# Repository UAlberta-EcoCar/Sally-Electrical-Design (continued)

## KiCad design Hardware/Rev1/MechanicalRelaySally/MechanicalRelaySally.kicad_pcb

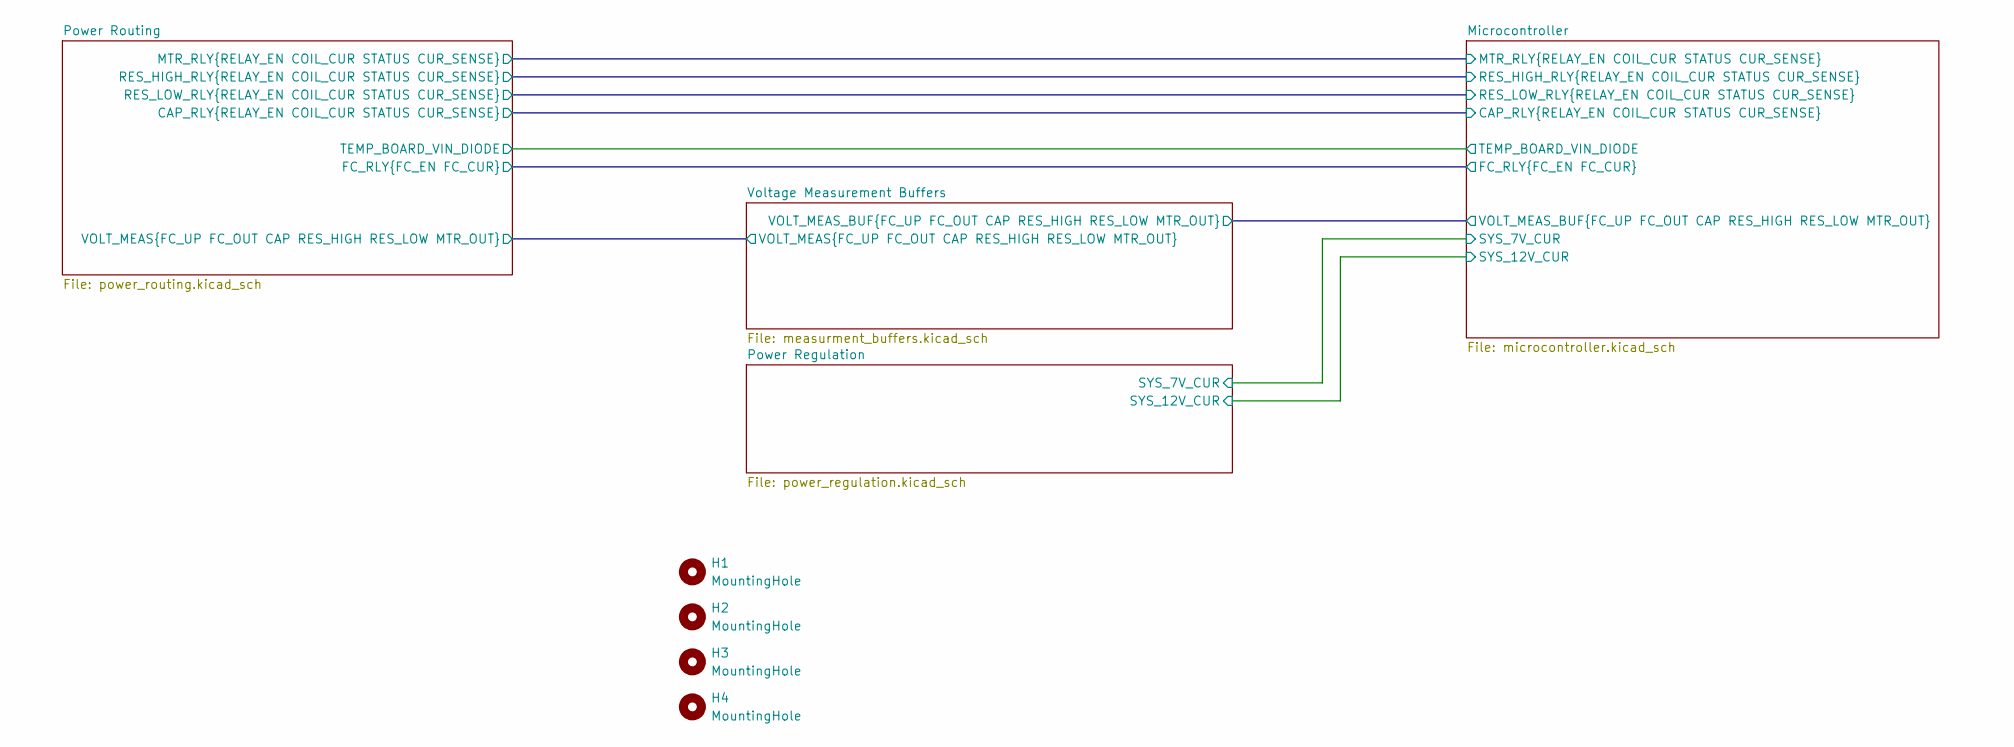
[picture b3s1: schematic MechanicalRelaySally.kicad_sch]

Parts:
H1, H2, H3, H4: MountingHole; MountingHole_3mm_Pad_Via

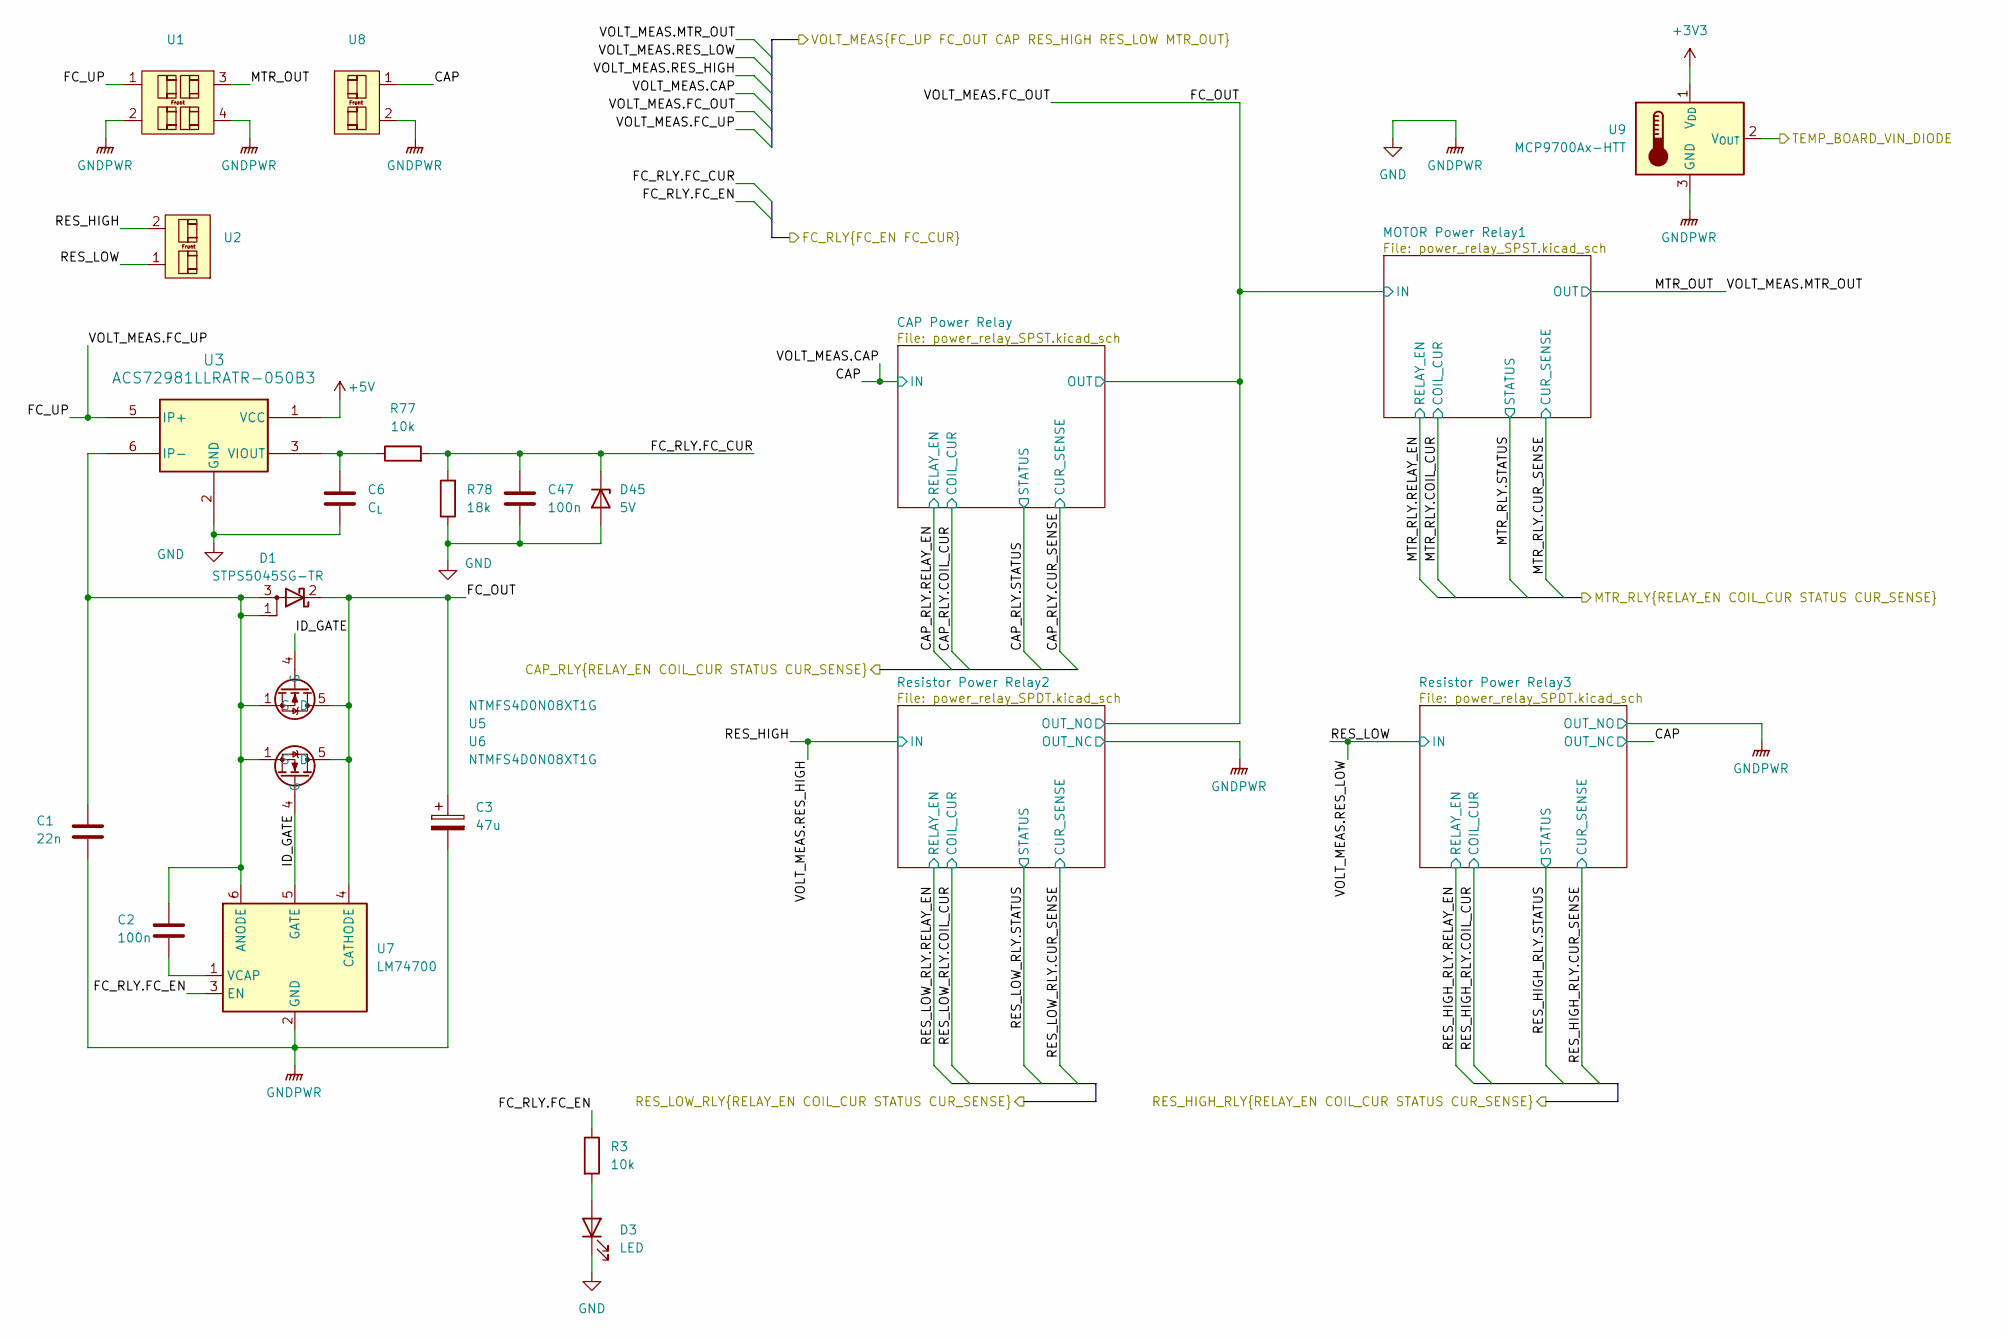
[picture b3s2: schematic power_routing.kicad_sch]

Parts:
C1: 22n; C_1210_3225Metric
C2: 100n; C_0603_1608Metric
C3: 47u; CP_Elec_6.3x7.7
C6: C_{L}; C_0402_1005Metric
C47: 100n; C_0402_1005Metric
D1: STPS5045SG-TR; TO-263-2; Part# 497-13279-1-ND
D3: LED; LED_0603_1608Metric
D45: 5V; D_SOD-323F
R3, R77: 10k; R_0603_1608Metric
R78: 18k; R_0603_1608Metric
U1: PowerPole15-45BoardEdge2x2
U2, U8: PowerPole15-45BoardEdge2x1
U3: ACS72981LLRATR-050B3; XDCR_ACS72981LLRATR-100B5
U5, U6: NTMFS4D0N08XT1G; PowerMosDFNHybrid
U7: LM74700; SOT-23-6
U9: MCP9700Ax-HTT; SOT-23

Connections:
+3V3: U9.1 (V_{DD}); also elsewhere on the board
+5V: U3.1 (VCC); also elsewhere on the board
/Microcontroller/FC_RLY.FC_CUR: C47.1, D45.1 (K), R77.2, R78.2; also elsewhere on the board
/Microcontroller/FC_RLY.FC_EN: R3.1, U7.3 (EN); also elsewhere on the board
/Microcontroller/TEMP_BOARD_VIN_DIODE: U9.2 (V_{OUT}); also elsewhere on the board
/Power Routing/ID_GATE: U5.4 (G), U6.4 (G), U7.5 (GATE)
/Power Routing/VOLT_MEAS.CAP: U8.1; also elsewhere on the board
/Power Routing/VOLT_MEAS.FC_OUT: C3.1, D1.2 (K), U5.5 (D), U6.5 (D), U7.4 (CATHODE); also elsewhere on the board
/Power Routing/VOLT_MEAS.FC_UP: U1.1, U3.5 (IP+); also elsewhere on the board
/Power Routing/VOLT_MEAS.MTR_OUT: U1.3; also elsewhere on the board
/Power Routing/VOLT_MEAS.RES_HIGH: U2.2; also elsewhere on the board
/Power Routing/VOLT_MEAS.RES_LOW: U2.1; also elsewhere on the board
GND: C1.2, C3.2, C6.2, C47.2, D3.1 (K), D45.2 (A), R78.1, U1.2, U1.4, U3.2 (GND), U3.4 (NC), U7.2 (GND), U8.2, U9.3 (GND); also elsewhere on the board
unnamed: D3.2 (A), R3.2
unnamed: C1.1, C2.1, D1.1 (A), D1.3 (A), U3.6 (IP-), U5.1 (S), U5.2 (S), U5.3 (S), U6.1 (S), U6.2 (S), U6.3 (S), U7.6 (ANODE)
unnamed: C6.1, R77.1, U3.3 (VIOUT)
unnamed: C2.2, U7.1 (VCAP)

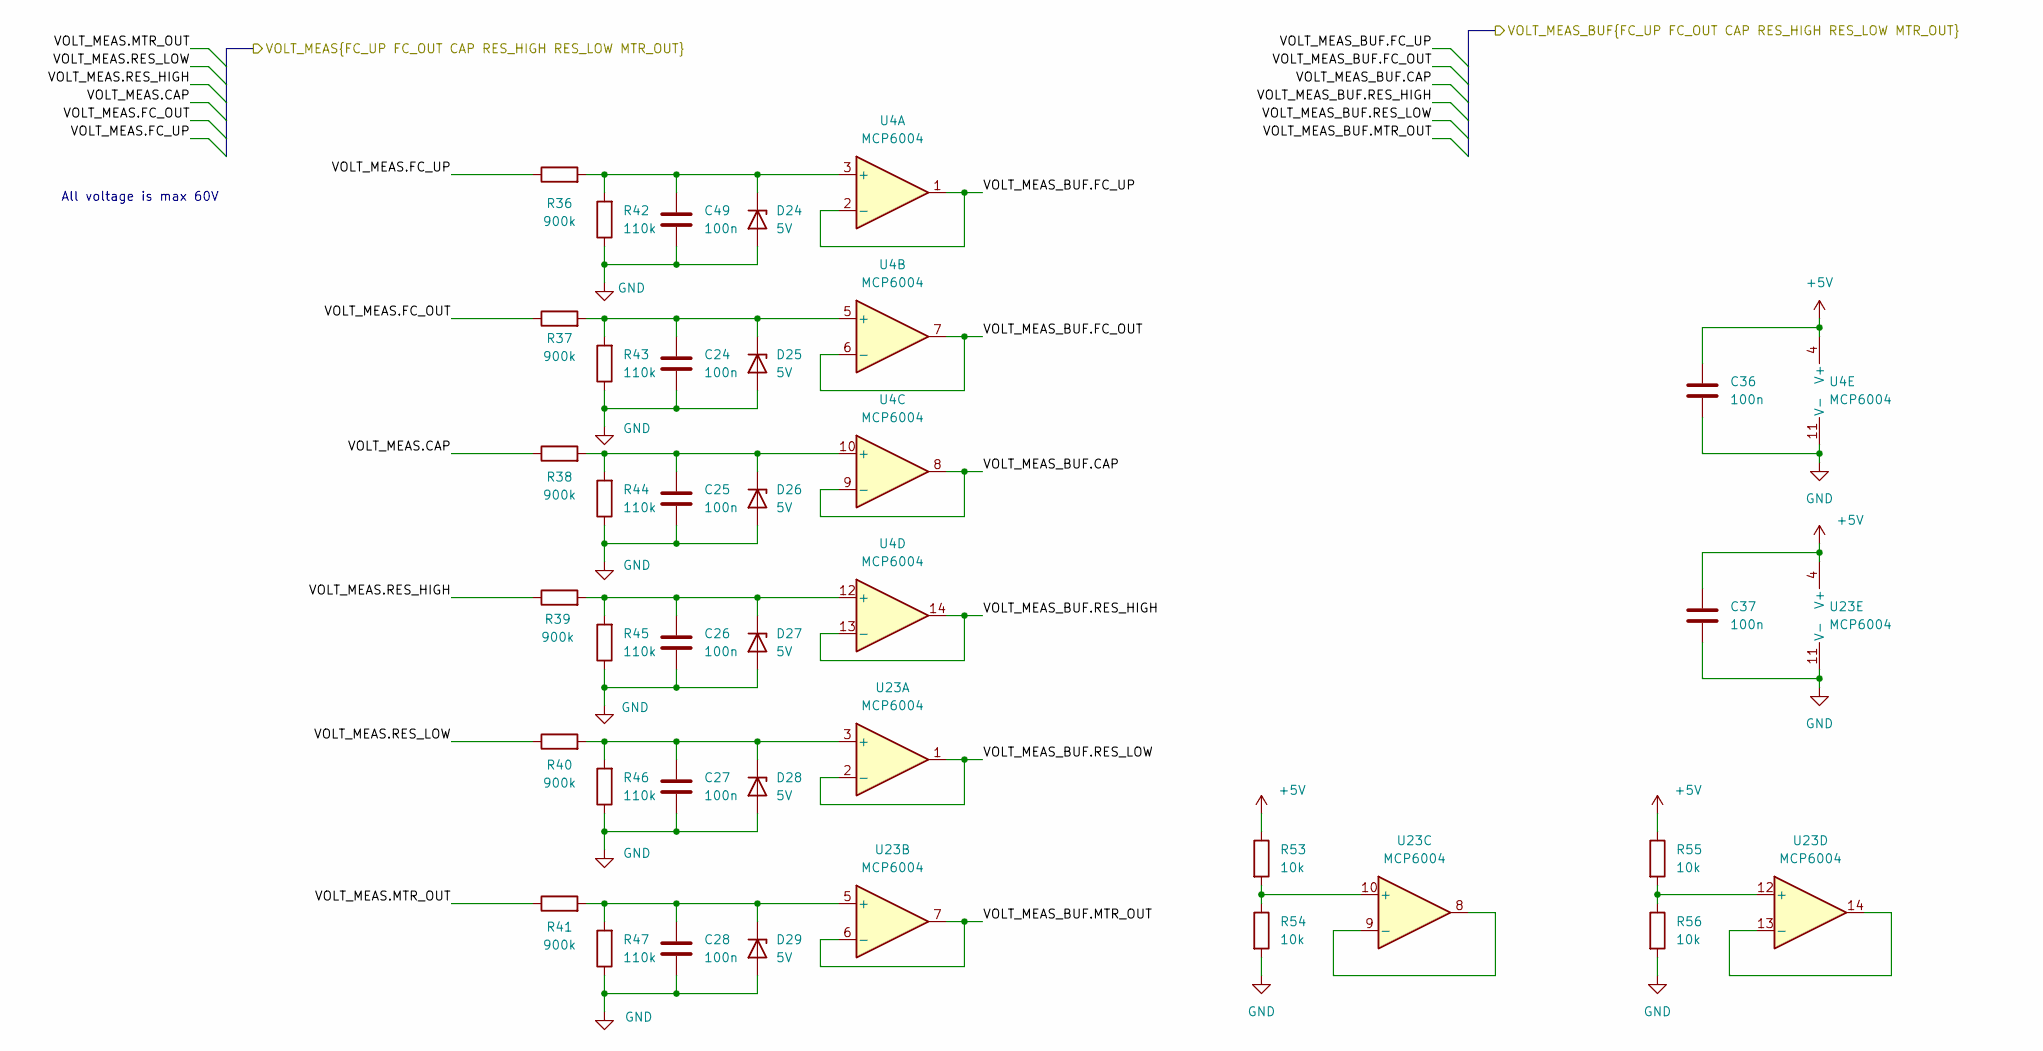
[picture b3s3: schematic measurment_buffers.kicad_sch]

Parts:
C24, C25, C26, C27, C28, C36, C37, C49: 100n; C_0402_1005Metric
D24, D25, D26, D27, D28, D29: 5V; D_SOD-323F
R36, R37, R38, R39, R40, R41: 900k; R_0603_1608Metric
R42, R43, R44, R45, R46, R47: 110k; R_0603_1608Metric
R53, R54, R55, R56: 10k; R_0603_1608Metric
U4, U23: MCP6004; TSSOP-14_4.4x5mm_P0.65mm

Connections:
+5V: C36.1, C37.1, R53.1, R55.1, U4.4 (V+), U23.4 (V+); also elsewhere on the board
/Microcontroller/VOLT_MEAS_BUF.CAP: U4.8, U4.9 (-); also elsewhere on the board
/Microcontroller/VOLT_MEAS_BUF.FC_OUT: U4.6 (-), U4.7; also elsewhere on the board
/Microcontroller/VOLT_MEAS_BUF.FC_UP: U4.1, U4.2 (-); also elsewhere on the board
/Microcontroller/VOLT_MEAS_BUF.MTR_OUT: U23.6 (-), U23.7; also elsewhere on the board
/Microcontroller/VOLT_MEAS_BUF.RES_HIGH: U4.13 (-), U4.14; also elsewhere on the board
/Microcontroller/VOLT_MEAS_BUF.RES_LOW: U23.1, U23.2 (-); also elsewhere on the board
/Power Routing/VOLT_MEAS.CAP: R38.1; also elsewhere on the board
/Power Routing/VOLT_MEAS.FC_OUT: R37.1; also elsewhere on the board
/Power Routing/VOLT_MEAS.FC_UP: R36.1; also elsewhere on the board
/Power Routing/VOLT_MEAS.MTR_OUT: R41.1; also elsewhere on the board
/Power Routing/VOLT_MEAS.RES_HIGH: R39.1; also elsewhere on the board
/Power Routing/VOLT_MEAS.RES_LOW: R40.1; also elsewhere on the board
GND: C24.2, C25.2, C26.2, C27.2, C28.2, C36.2, C37.2, C49.2, D24.2 (A), D25.2 (A), D26.2 (A), D27.2 (A), D28.2 (A), D29.2 (A), R42.1, R43.1, R44.1, R45.1, R46.1, R47.1, R54.2, R56.2, U4.11 (V-), U23.11 (V-); also elsewhere on the board
unnamed: C49.1, D24.1 (K), R36.2, R42.2, U4.3 (+)
unnamed: C24.1, D25.1 (K), R37.2, R43.2, U4.5 (+)
unnamed: C25.1, D26.1 (K), R38.2, R44.2, U4.10 (+)
unnamed: C26.1, D27.1 (K), R39.2, R45.2, U4.12 (+)
unnamed: C27.1, D28.1 (K), R40.2, R46.2, U23.3 (+)
unnamed: C28.1, D29.1 (K), R41.2, R47.2, U23.5 (+)
unnamed: R53.2, R54.1, U23.10 (+)
unnamed: U23.8, U23.9 (-)
unnamed: R55.2, R56.1, U23.12 (+)
unnamed: U23.13 (-), U23.14

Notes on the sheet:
All voltage is max 60V

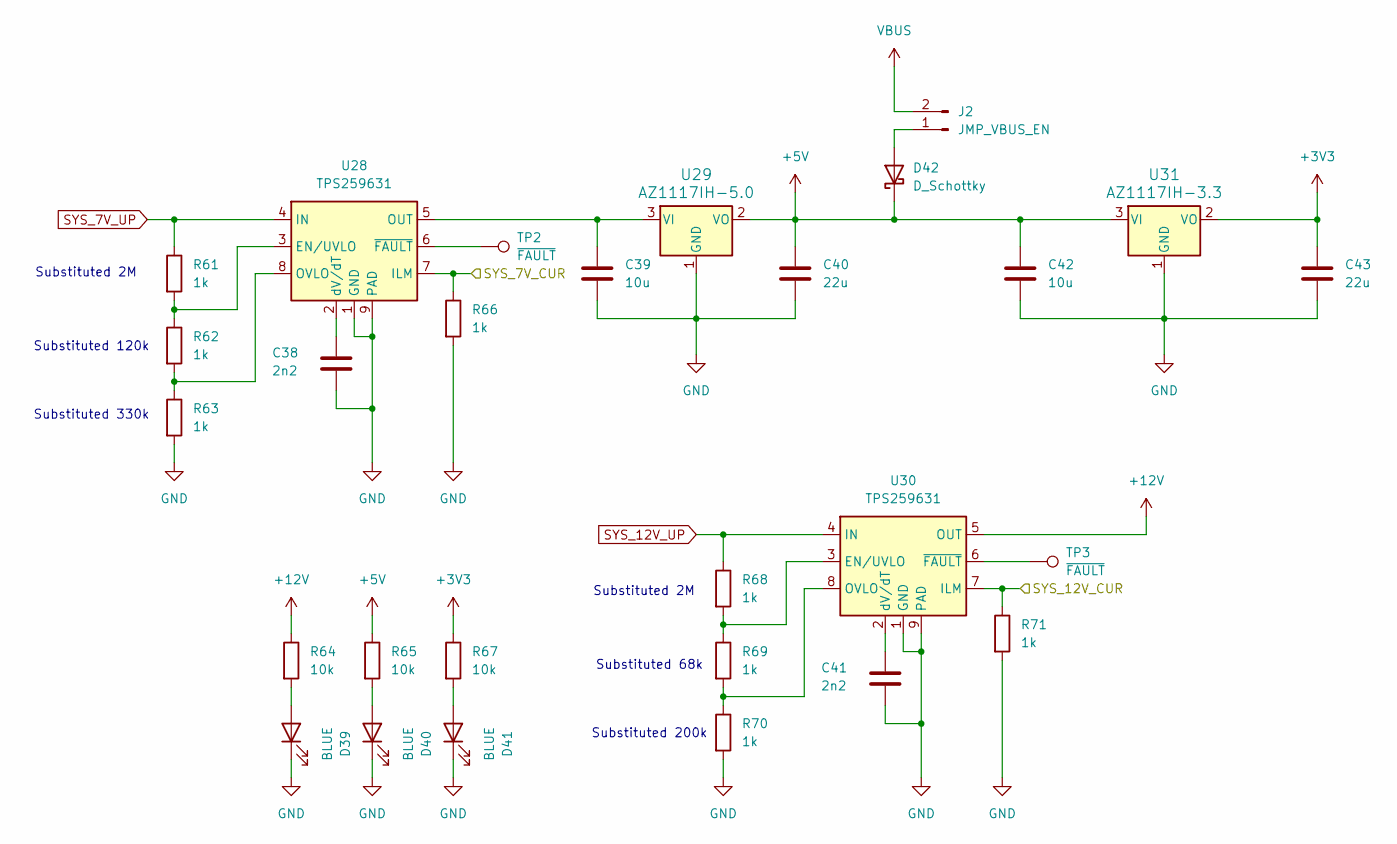
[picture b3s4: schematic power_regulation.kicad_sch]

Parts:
C38, C41: 2n2; C_0402_1005Metric
C39: 10u; C_0603_1608Metric
C40: 22u; C_0603_1608Metric
C42: 10u; C_0805_2012Metric
C43: 22u; C_0805_2012Metric
D39, D40, D41: BLUE; LED_0603_1608Metric
D42: D_Schottky; D_SOD-123
J2: JMP_VBUS_EN; PinHeader_1x02_P2.54mm_Horizontal
R61, R62, R63, R66, R68, R69, R70, R71: 1k; R_0603_1608Metric
R64, R65, R67: 10k; R_0603_1608Metric
TP2, TP3: ~{FAULT}; TestPoint_Pad_1.0x1.0mm
U28, U30: TPS259631; SOIC-8-1EP_3.9x4.9mm_P1.27mm_EP2.29x3mm
U29: AZ1117IH-5.0; SOT-223-3_TabPin2
U31: AZ1117IH-3.3; SOT-223-3_TabPin2

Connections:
+3V3: C43.1, R67.1, U31.2 (VO); also elsewhere on the board
+5V: C40.1, C42.1, D42.1 (K), R65.1, U29.2 (VO), U31.3 (VI); also elsewhere on the board
+12V: R64.1, U30.5 (OUT); also elsewhere on the board
/Microcontroller/SYS_7V_CUR: R66.1, U28.7 (ILM); also elsewhere on the board
/Microcontroller/SYS_12V_CUR: R71.1, U30.7 (ILM); also elsewhere on the board
GND: C38.2, C39.2, C40.2, C41.2, C42.2, C43.2, D39.1 (K), D40.1 (K), D41.1 (K), R63.2, R66.2, R70.2, R71.2, U28.1 (GND), U28.9 (PAD), U29.1 (GND), U30.1 (GND), U30.9 (PAD), U31.1 (GND); also elsewhere on the board
unnamed: D39.2 (A), R64.2
unnamed: D40.2 (A), R65.2
unnamed: D41.2 (A), R67.2
unnamed: D42.2 (A), J2.1
unnamed: R61.2, R62.1, U28.3 (EN/UVLO)
unnamed: C39.1, U28.5 (OUT), U29.3 (VI)
unnamed: R62.2, R63.1, U28.8 (OVLO)
unnamed: C38.1, U28.2 (dV/dT)
unnamed: TP2.1, U28.6 (~FAULT)
unnamed: R68.2, R69.1, U30.3 (EN/UVLO)
unnamed: R69.2, R70.1, U30.8 (OVLO)
unnamed: C41.1, U30.2 (dV/dT)
unnamed: TP3.1, U30.6 (~FAULT)
SYS_7V_UP: R61.1, U28.4 (IN); also elsewhere on the board
SYS_12V_UP: R68.1, U30.4 (IN); also elsewhere on the board
VBUS: J2.2; also elsewhere on the board

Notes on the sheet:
Substituted 200k
Substituted 2M
Substituted 330k
Substituted 68k
Substituted 120k

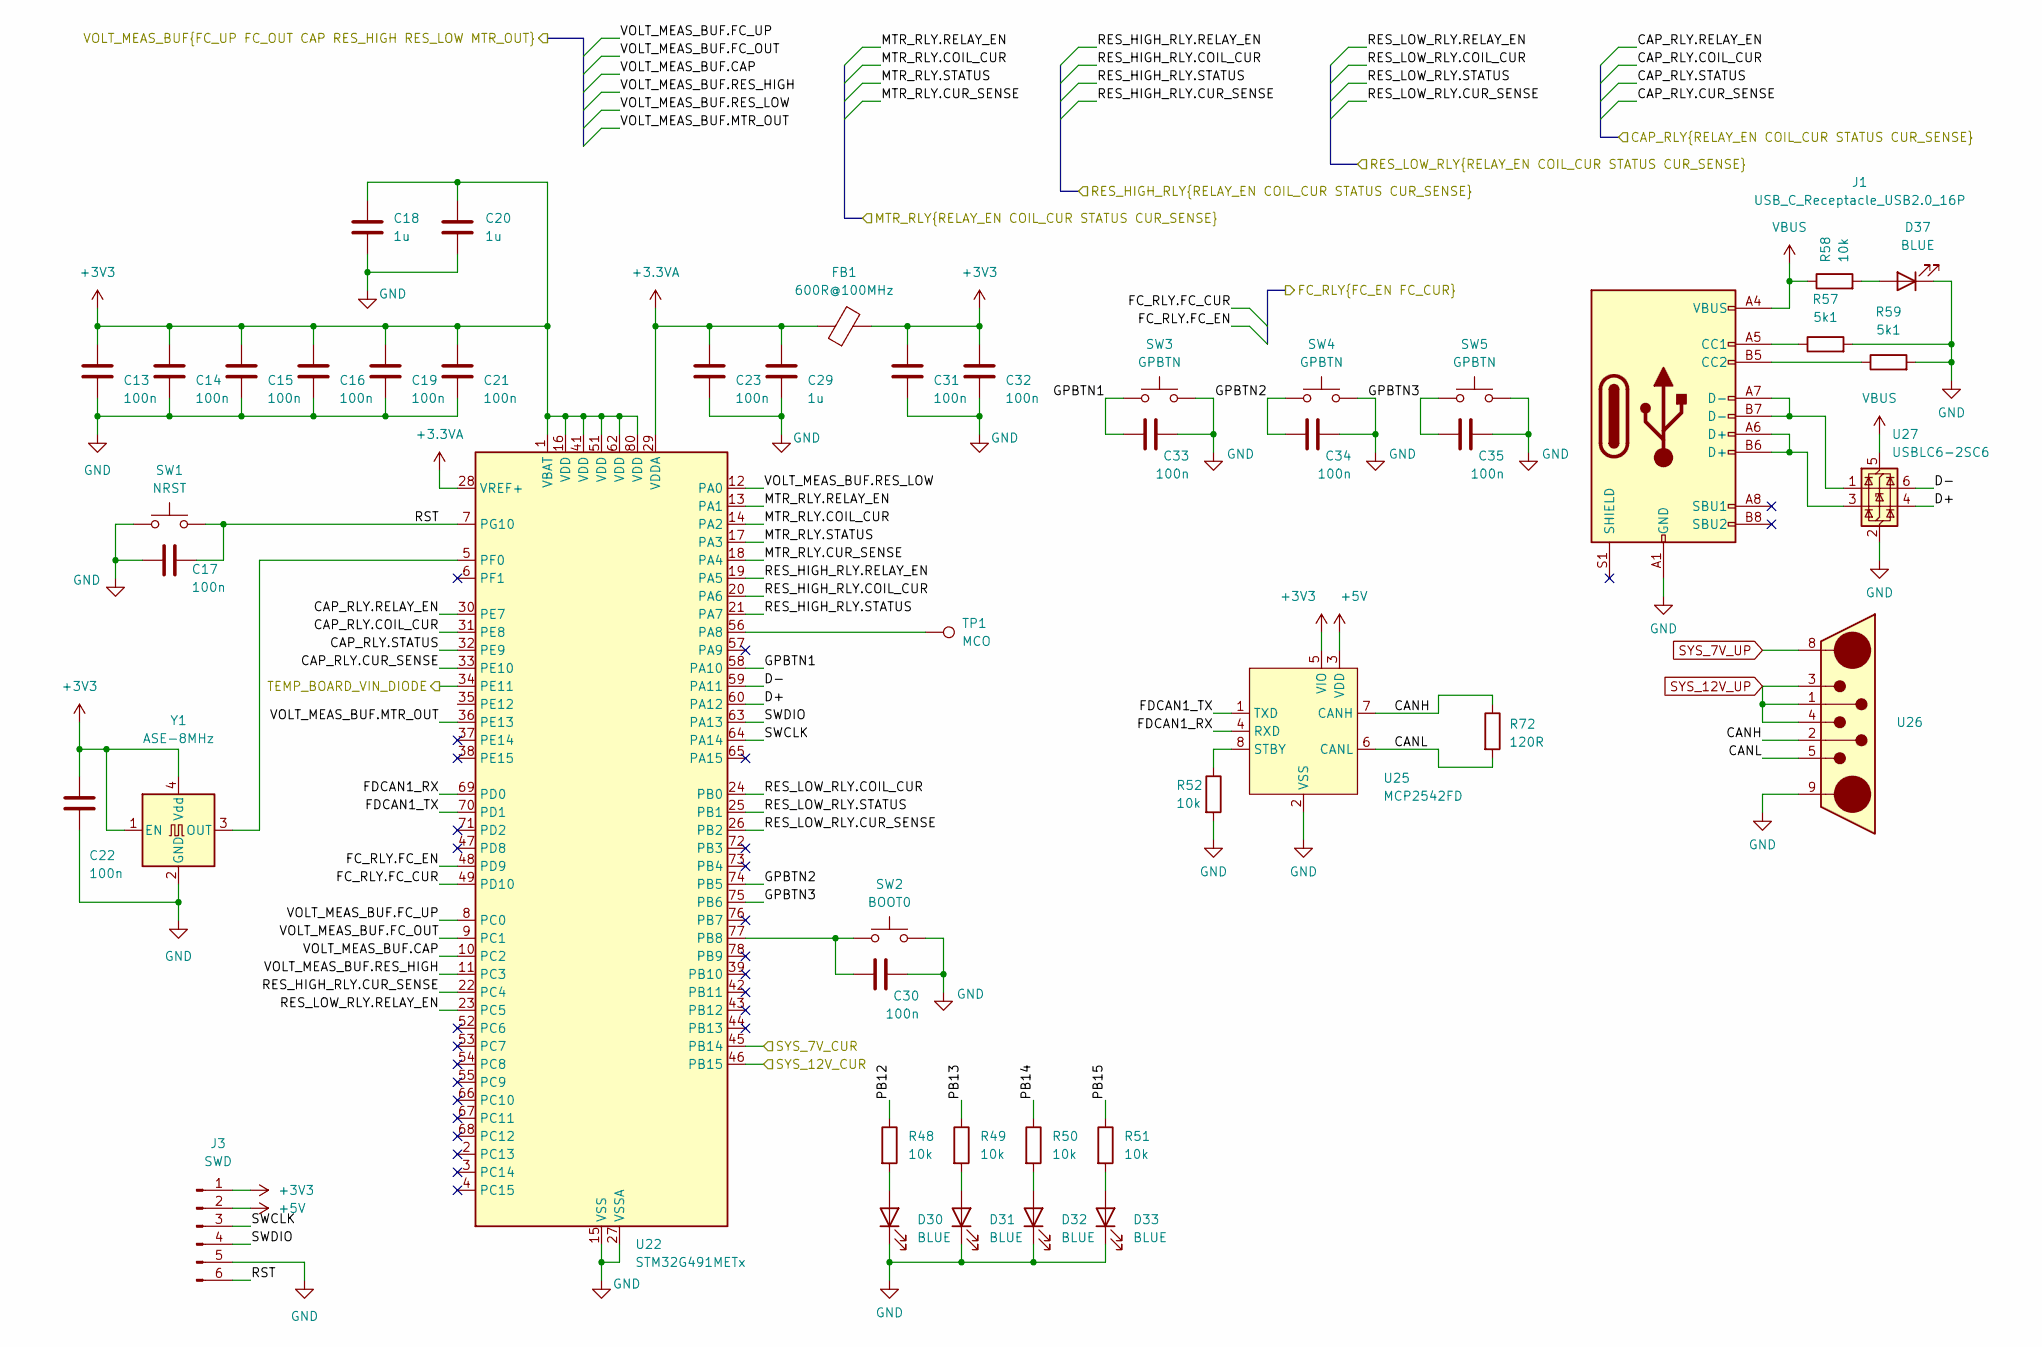
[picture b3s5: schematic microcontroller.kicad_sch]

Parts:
C13, C14, C15, C16, C17, C19, C21, C22, C23, C30, C31, C32, C33, C34, C35: 100n; C_0402_1005Metric
C18, C20, C29: 1u; C_0603_1608Metric
D30, D31, D32, D33, D37: BLUE; LED_0603_1608Metric
FB1: 600R@100MHz; L_0603_1608Metric
J1: USB_C_Receptacle_USB2.0_16P; USB_C_Receptacle_GCT_USB4105-xx-A_16P_TopMnt_Horizontal
J3: SWD; PinSocket_1x06_P2.54mm_Horizontal
R48, R49, R50, R51, R52, R58: 10k; R_0603_1608Metric
R57, R59: 5k1; R_0402_1005Metric
R72: 120R; R_0603_1608Metric
SW1: NRST; SW_Push_1P1T_NO_Vertical_Wuerth_434133025816
SW2: BOOT0; SW_Push_1P1T_NO_Vertical_Wuerth_434133025816
SW3, SW4, SW5: GPBTN; SW_Push_1P1T_NO_Vertical_Wuerth_434133025816
TP1: MCO; TP_Small_0.5mm
U22: STM32G491METx; LQFP-80_12x12mm_P0.5mm
U25: MCP2542FD; SOIC-8_3.9x4.9mm_P1.27mm
U26: Male Conn; DB7W2-Male
U27: USBLC6-2SC6; SOT-23-6
Y1: ASE-8MHz; Oscillator_SMD_Abracon_ASE-4Pin_3.2x2.5mm

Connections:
+3.3VA: C23.1, C29.1, FB1.1, U22.28 (VREF+), U22.29 (VDDA)
+3V3: C13.1, C14.1, C15.1, C16.1, C18.1, C19.1, C20.1, C21.1, C22.1, C31.1, C32.1, FB1.2, J3.1, U22.1 (VBAT), U22.16 (VDD), U22.41 (VDD), U22.51 (VDD), U22.62 (VDD), U22.80 (VDD), U25.5 (VIO), Y1.1 (EN), Y1.4 (Vdd); also elsewhere on the board
+5V: J3.2, U25.3 (VDD); also elsewhere on the board
/Microcontroller/CANH: R72.1, U25.7 (CANH), U26.2
/Microcontroller/CANL: R72.2, U25.6 (CANL), U26.5
/Microcontroller/CAP_RLY.COIL_CUR: U22.31 (PE8); also elsewhere on the board
/Microcontroller/CAP_RLY.CUR_SENSE: U22.33 (PE10); also elsewhere on the board
/Microcontroller/CAP_RLY.RELAY_EN: U22.30 (PE7); also elsewhere on the board
/Microcontroller/CAP_RLY.STATUS: U22.32 (PE9); also elsewhere on the board
/Microcontroller/D+: U22.60 (PA12), U27.4 (I/O2)
/Microcontroller/D-: U22.59 (PA11), U27.6 (I/O1)
/Microcontroller/FC_RLY.FC_CUR: U22.49 (PD10); also elsewhere on the board
/Microcontroller/FC_RLY.FC_EN: U22.48 (PD9); also elsewhere on the board
/Microcontroller/FDCAN1_RX: U22.69 (PD0), U25.4 (RXD)
/Microcontroller/FDCAN1_TX: U22.70 (PD1), U25.1 (TXD)
/Microcontroller/GPBTN1: C33.2, SW3.2, U22.58 (PA10)
/Microcontroller/GPBTN2: C34.2, SW4.2, U22.74 (PB5)
/Microcontroller/GPBTN3: C35.2, SW5.2, U22.75 (PB6)
/Microcontroller/MTR_RLY.COIL_CUR: U22.14 (PA2); also elsewhere on the board
/Microcontroller/MTR_RLY.CUR_SENSE: U22.18 (PA4); also elsewhere on the board
/Microcontroller/MTR_RLY.RELAY_EN: U22.13 (PA1); also elsewhere on the board
/Microcontroller/MTR_RLY.STATUS: U22.17 (PA3); also elsewhere on the board
/Microcontroller/PB12: R48.1
/Microcontroller/PB13: R49.1
/Microcontroller/PB14: R50.1
/Microcontroller/PB15: R51.1
/Microcontroller/RES_HIGH_RLY.COIL_CUR: U22.20 (PA6); also elsewhere on the board
/Microcontroller/RES_HIGH_RLY.CUR_SENSE: U22.22 (PC4); also elsewhere on the board
/Microcontroller/RES_HIGH_RLY.RELAY_EN: U22.19 (PA5); also elsewhere on the board
/Microcontroller/RES_HIGH_RLY.STATUS: U22.21 (PA7); also elsewhere on the board
/Microcontroller/RES_LOW_RLY.COIL_CUR: U22.24 (PB0); also elsewhere on the board
/Microcontroller/RES_LOW_RLY.CUR_SENSE: U22.26 (PB2); also elsewhere on the board
/Microcontroller/RES_LOW_RLY.RELAY_EN: U22.23 (PC5); also elsewhere on the board
/Microcontroller/RES_LOW_RLY.STATUS: U22.25 (PB1); also elsewhere on the board
/Microcontroller/RST: C17.2, J3.6, SW1.2, U22.7 (PG10)
/Microcontroller/SWCLK: J3.3, U22.64 (PA14)
/Microcontroller/SWDIO: J3.4, U22.63 (PA13)
/Microcontroller/SYS_7V_CUR: U22.45 (PB14); also elsewhere on the board
/Microcontroller/SYS_12V_CUR: U22.46 (PB15); also elsewhere on the board
/Microcontroller/TEMP_BOARD_VIN_DIODE: U22.34 (PE11); also elsewhere on the board
/Microcontroller/VOLT_MEAS_BUF.CAP: U22.10 (PC2); also elsewhere on the board
/Microcontroller/VOLT_MEAS_BUF.FC_OUT: U22.9 (PC1); also elsewhere on the board
/Microcontroller/VOLT_MEAS_BUF.FC_UP: U22.8 (PC0); also elsewhere on the board
/Microcontroller/VOLT_MEAS_BUF.MTR_OUT: U22.36 (PE13); also elsewhere on the board
/Microcontroller/VOLT_MEAS_BUF.RES_HIGH: U22.11 (PC3); also elsewhere on the board
/Microcontroller/VOLT_MEAS_BUF.RES_LOW: U22.12 (PA0); also elsewhere on the board
GND: C13.2, C14.2, C15.2, C16.2, C17.1, C18.2, C19.2, C20.2, C21.2, C22.2, C23.2, C29.2, C30.1, C31.2, C32.2, C33.1, C34.1, C35.1, D30.1 (K), D31.1 (K), D32.1 (K), D33.1 (K), D37.1 (K), J1.A1 (GND), J1.A12 (GND), J1.B1 (GND), J1.B12 (GND), J3.5, R52.2, R57.2, R59.2, SW1.1, SW2.1, SW3.1, SW4.1, SW5.1, U22.15 (VSS), U22.27 (VSSA), U22.40 (VSS), U22.50 (VSS), U22.61 (VSS), U22.79 (VSS), U25.2 (VSS), U26.9, U27.2 (GND), Y1.2 (GND); also elsewhere on the board
unnamed: D30.2 (A), R48.2
unnamed: D31.2 (A), R49.2
unnamed: D32.2 (A), R50.2
unnamed: D33.2 (A), R51.2
unnamed: D37.2 (A), R58.2
unnamed: J1.A5 (CC1), R57.1
unnamed: J1.B5 (CC2), R59.1
unnamed: J1.A6 (D+), J1.B6 (D+), U27.3 (I/O2)
unnamed: J1.A7 (D-), J1.B7 (D-), U27.1 (I/O1)
unnamed: TP1.1, U22.56 (PA8)
unnamed: C30.2, SW2.2, U22.77 (PB8)
unnamed: U22.5 (PF0), Y1.3 (OUT)
unnamed: R52.1, U25.8 (STBY)
SYS_7V_UP: U26.8; also elsewhere on the board
SYS_12V_UP: U26.1, U26.3, U26.4; also elsewhere on the board
VBUS: J1.A4 (VBUS), J1.A9 (VBUS), J1.B4 (VBUS), J1.B9 (VBUS), R58.1, U27.5 (VBUS); also elsewhere on the board

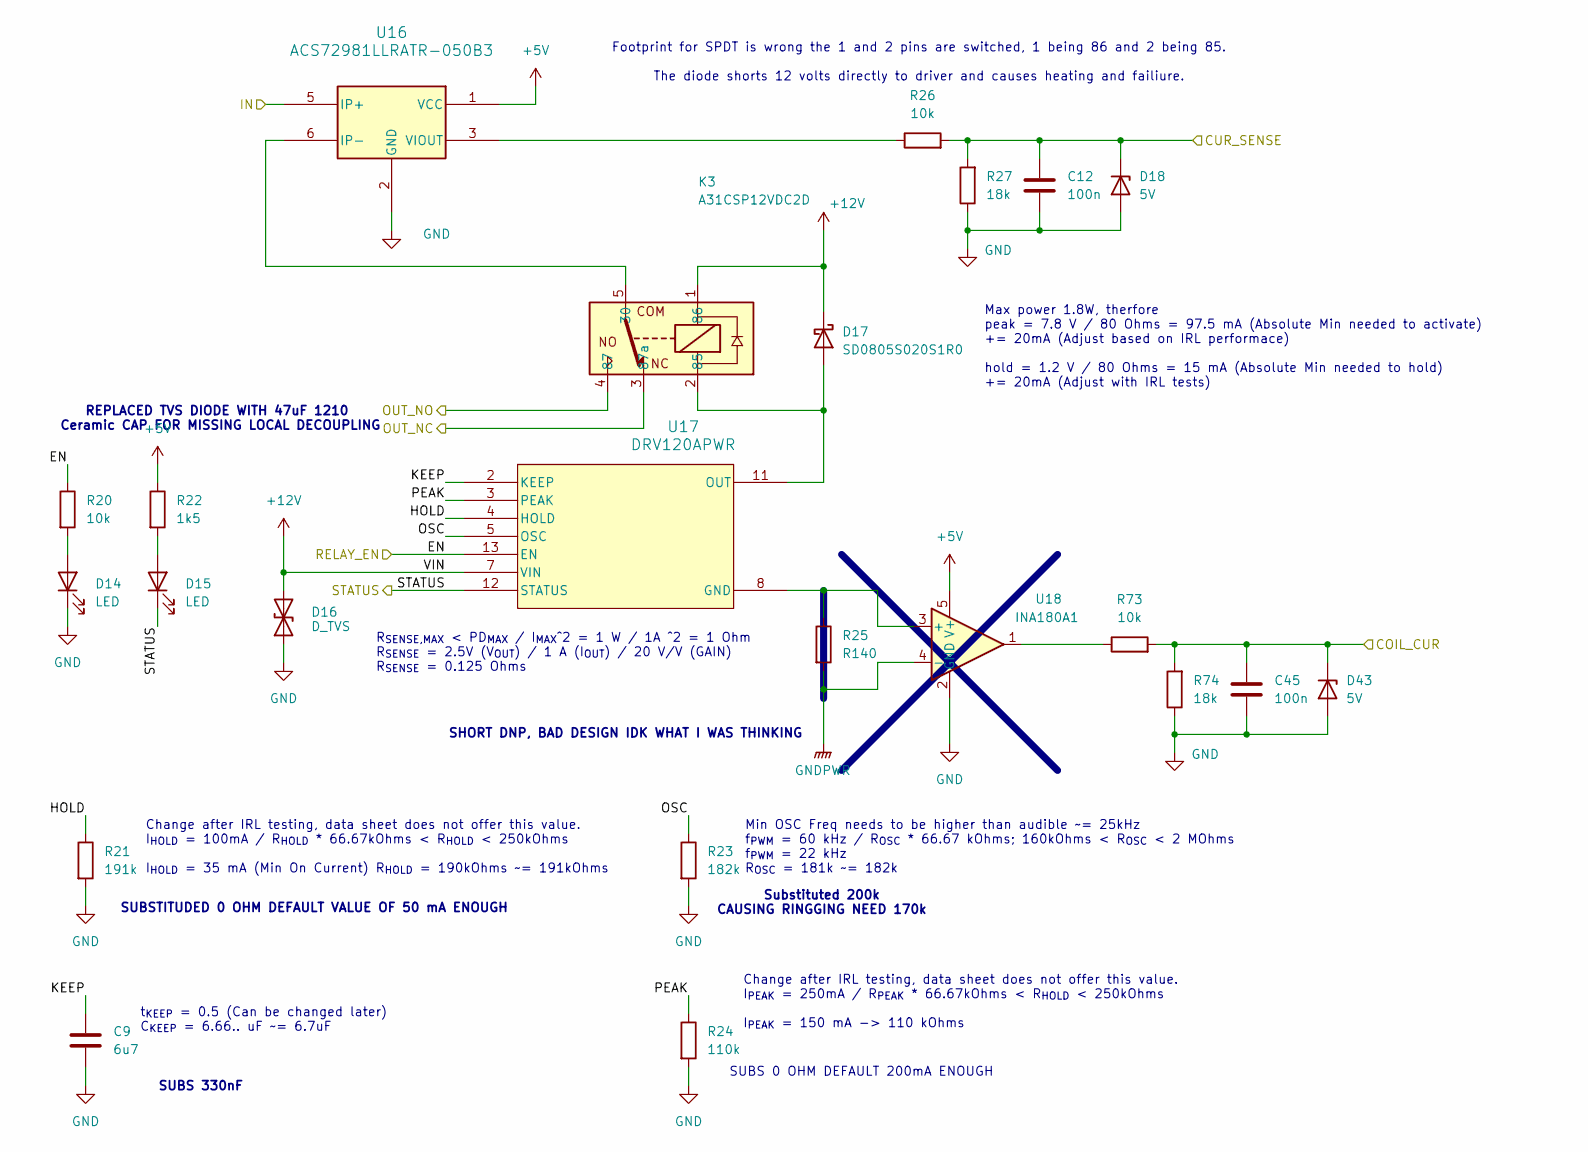
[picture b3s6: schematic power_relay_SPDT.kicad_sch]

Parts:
C9: 6u7; C_0603_1608Metric
C12, C45: 100n; C_0402_1005Metric
D14, D15: LED; LED_0603_1608Metric
D16: D_TVS; D_SOD_123_M
D17: SD0805S020S1R0; D_SOD-123; Part# 478-7800-1-ND
D18, D43: 5V; D_SOD-323F
K3: A31CSP12VDC2D; A3_HeavyDuty_PCPIN
R20, R26, R73: 10k; R_0603_1608Metric
R21: 191k; R_0603_1608Metric
R22: 1k5; R_0603_1608Metric
R23: 182k; R_0603_1608Metric
R24: 110k; R_0603_1608Metric
R25: R140; R_1206_3216Metric
R27, R74: 18k; R_0603_1608Metric
U16: ACS72981LLRATR-050B3; XDCR_ACS72981LLRATR-100B5
U17: DRV120APWR; PW14_TEX
U18: INA180A1; SOT-23-5

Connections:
+5V: R22.1, U16.1 (VCC), U18.5 (V+); also elsewhere on the board
+12V: D16.2 (A2), D17.1 (K), K3.1 (86), U17.7 (VIN); also elsewhere on the board
/Microcontroller/RES_LOW_RLY.COIL_CUR: C45.1, D43.1 (K), R73.2, R74.2; also elsewhere on the board
/Microcontroller/RES_LOW_RLY.CUR_SENSE: C12.1, D18.1 (K), R26.2, R27.2; also elsewhere on the board
/Microcontroller/RES_LOW_RLY.RELAY_EN: R20.1, U17.13 (EN); also elsewhere on the board
/Microcontroller/RES_LOW_RLY.STATUS: D15.1 (K), U17.12 (STATUS); also elsewhere on the board
/Power Routing/Resistor Power Relay2/HOLD: R21.1, U17.4 (HOLD)
/Power Routing/Resistor Power Relay2/KEEP: C9.1, U17.2 (KEEP)
/Power Routing/Resistor Power Relay2/OSC: R23.1, U17.5 (OSC)
/Power Routing/Resistor Power Relay2/PEAK: R24.1, U17.3 (PEAK)
/Power Routing/VOLT_MEAS.FC_OUT: K3.4 (87); also elsewhere on the board
/Power Routing/VOLT_MEAS.RES_HIGH: U16.5 (IP+); also elsewhere on the board
GND: C9.2, C12.2, C45.2, D14.1 (K), D16.1 (A1), D18.2 (A), D43.2 (A), K3.3 (87a), R21.2, R23.2, R24.2, R25.2, R27.1, R74.1, U16.2 (GND), U16.4 (NC), U18.2 (GND), U18.4 (-); also elsewhere on the board
unnamed: D14.2 (A), R20.2
unnamed: D15.2 (A), R22.2
unnamed: D17.2 (A), K3.2 (85), U17.11 (OUT)
unnamed: K3.5 (30), U16.6 (IP-)
unnamed: R73.1, U18.1
unnamed: R26.1, U16.3 (VIOUT)
unnamed: R25.1, U17.8 (GND), U18.3 (+)

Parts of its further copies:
C11: 6u7; C_0603_1608Metric
C44, C48: 100n; C_0402_1005Metric
D19, D20: LED; LED_0603_1608Metric
D21: D_TVS; D_SOD_123_M
D22: SD0805S020S1R0; D_SOD-123; Part# 478-7800-1-ND
D23, D46: 5V; D_SOD-323F
K4: A31CSP12VDC2D; A3_HeavyDuty_PCPIN
R28, R34, R79: 10k; R_0603_1608Metric
R29: 191k; R_0603_1608Metric
R30: 1k5; R_0603_1608Metric
R31: 182k; R_0603_1608Metric
R32: 110k; R_0603_1608Metric
R33: R140; R_1206_3216Metric
R35, R80: 18k; R_0603_1608Metric
U19: ACS72981LLRATR-050B3; XDCR_ACS72981LLRATR-100B5
U20: DRV120APWR; PW14_TEX
U21: INA180A1; SOT-23-5

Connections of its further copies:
+5V: R30.1, U19.1 (VCC), U21.5 (V+); also elsewhere on the board
+12V: D21.2 (A2), D22.1 (K), K4.1 (86), U20.7 (VIN); also elsewhere on the board
/Microcontroller/RES_HIGH_RLY.COIL_CUR: C48.1, D46.1 (K), R79.2, R80.2; also elsewhere on the board
/Microcontroller/RES_HIGH_RLY.CUR_SENSE: C44.1, D23.1 (K), R34.2, R35.2; also elsewhere on the board
/Microcontroller/RES_HIGH_RLY.RELAY_EN: R28.1, U20.13 (EN); also elsewhere on the board
/Microcontroller/RES_HIGH_RLY.STATUS: D20.1 (K), U20.12 (STATUS); also elsewhere on the board
/Power Routing/Resistor Power Relay3/HOLD: R29.1, U20.4 (HOLD)
/Power Routing/Resistor Power Relay3/KEEP: C11.1, U20.2 (KEEP)
/Power Routing/Resistor Power Relay3/OSC: R31.1, U20.5 (OSC)
/Power Routing/Resistor Power Relay3/PEAK: R32.1, U20.3 (PEAK)
/Power Routing/VOLT_MEAS.CAP: K4.3 (87a); also elsewhere on the board
/Power Routing/VOLT_MEAS.RES_LOW: U19.5 (IP+); also elsewhere on the board
GND: C11.2, C44.2, C48.2, D19.1 (K), D21.1 (A1), D23.2 (A), D46.2 (A), K4.4 (87), R29.2, R31.2, R32.2, R33.2, R35.1, R80.1, U19.2 (GND), U21.2 (GND), U21.4 (-); also elsewhere on the board
unnamed: D19.2 (A), R28.2
unnamed: D20.2 (A), R30.2
unnamed: D22.2 (A), K4.2 (85), U20.11 (OUT)
unnamed: K4.5 (30), U19.6 (IP-)
unnamed: R79.1, U21.1
unnamed: R34.1, U19.3 (VIOUT)
unnamed: R33.1, U20.8 (GND), U21.3 (+)

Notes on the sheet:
Change after IRL testing, data sheet does not offer this value. I_{HOLD} = 100mA / R_{HOLD} * 66.67kOhms < R_{HOLD} < 250kOhms I_{HOLD} = 35 mA (Min On Current) R_{HOLD} = 190kOhms ~= 191kOhms
R_{SENSE,MAX} < PD_{MAX} / I_{MAX}^2 = 1 W / 1A ^2 = 1 Ohm R_{SENSE} = 2.5V (V_{OUT}) / 1 A (I_{OUT}) / 20 V/V (GAIN) R_{SENSE} = 0.125 Ohms
Max power 1.8W, therfore peak = 7.8 V / 80 Ohms = 97.5 mA (Absolute Min needed to activate) += 20mA (Adjust based on IRL performace) hold = 1.2 V / 80 Ohms = 15 mA (Absolute Min needed to hold) += 20mA (Adjust with IRL tests)
Change after IRL testing, data sheet does not offer this value. I_{PEAK} = 250mA / R_{PEAK} * 66.67kOhms < R_{HOLD} < 250kOhms I_{PEAK} = 150 mA -> 110 kOhms
SUBSTITUDED 0 OHM DEFAULT VALUE OF 50 mA ENOUGH
SUBS 330nF
Min OSC Freq needs to be higher than audible ~= 25kHz f_{PWM} = 60 kHz / R_{OSC} * 66.67 kOhms; 160kOhms < R_{OSC} < 2 MOhms f_{PWM} = 22 kHz R_{OSC} = 181k ~= 182k
Substituted 200k CAUSING RINGGING NEED 170k
SUBS 0 OHM DEFAULT 200mA ENOUGH
SHORT DNP, BAD DESIGN IDK WHAT I WAS THINKING
REPLACED TVS DIODE WITH 47uF 1210 Ceramic CAP FOR MISSING LOCAL DECOUPLING
t_{KEEP} = 0.5 (Can be changed later) C_{KEEP} = 6.66.. uF ~= 6.7uF
Footprint for SPDT is wrong the 1 and 2 pins are switched, 1 being 86 and 2 being 85. The diode shorts 12 volts directly to driver and causes heating and failiure.
